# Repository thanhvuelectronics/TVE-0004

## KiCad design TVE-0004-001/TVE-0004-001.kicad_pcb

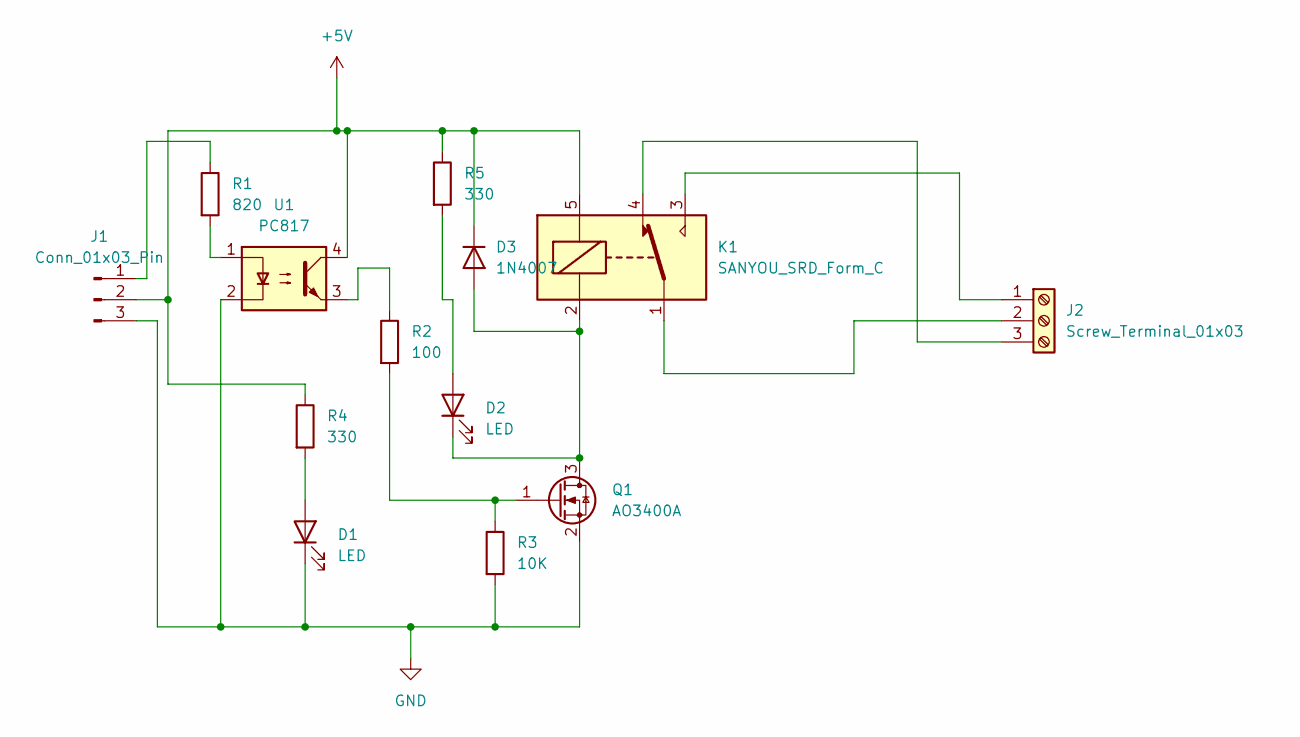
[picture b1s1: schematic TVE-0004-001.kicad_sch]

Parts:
D1, D2: LED; LED_D3.0mm
D3: 1N4007; D_DO-41_SOD81_P10.16mm_Horizontal
J1: Conn_01x03_Pin; PinHeader_1x03_P2.54mm_Vertical
J2: Screw_Terminal_01x03; TerminalBlock_Phoenix_MKDS-3-3-5.08_1x03_P5.08mm_Horizontal
K1: SANYOU_SRD_Form_C; Relay_SPDT_SANYOU_SRD_Series_Form_C
Q1: AO3400A; SOT-23
R1: 820; R_Axial_DIN0207_L6.3mm_D2.5mm_P7.62mm_Horizontal
R2: 100; R_Axial_DIN0207_L6.3mm_D2.5mm_P7.62mm_Horizontal
R3: 10K; R_Axial_DIN0207_L6.3mm_D2.5mm_P7.62mm_Horizontal
R4, R5: 330; R_Axial_DIN0207_L6.3mm_D2.5mm_P7.62mm_Horizontal
U1: PC817; DIP-4_W7.62mm

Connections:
+5V: D3.1 (K), J1.2, K1.5, R4.1, R5.1, U1.4
GND: D1.1 (K), J1.3, Q1.2 (S), R3.2, U1.2
unnamed: D1.2 (A), R4.2
unnamed: D2.2 (A), R5.2
unnamed: D2.1 (K), D3.2 (A), K1.2, Q1.3 (D)
unnamed: J1.1, R1.1
unnamed: J2.1, K1.3
unnamed: J2.2, K1.1
unnamed: J2.3, K1.4
unnamed: Q1.1 (G), R2.2, R3.1
unnamed: R1.2, U1.1
unnamed: R2.1, U1.3

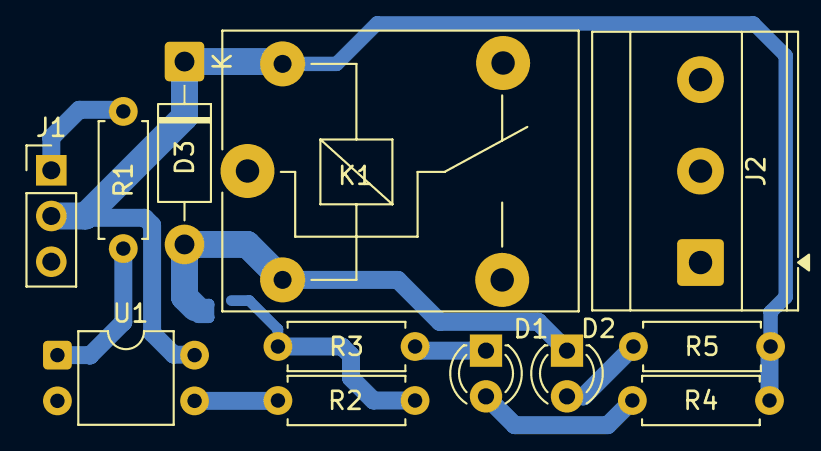
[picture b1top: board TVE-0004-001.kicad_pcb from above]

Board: 2 copper layers, 13 parts (1 on the bottom side), 12 nets.
